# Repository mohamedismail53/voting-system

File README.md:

# About
Wireless Voting machine using Atmega32 and RF modules on PCB It consists of 4 separated PCB units: 3 transmitters and 1 receiver (every PCB unit has ATmega32 controller). Every transmitter block has 3 options to choose from (yes, no, abs) and the receiver has LCD that displays the result of every choice.

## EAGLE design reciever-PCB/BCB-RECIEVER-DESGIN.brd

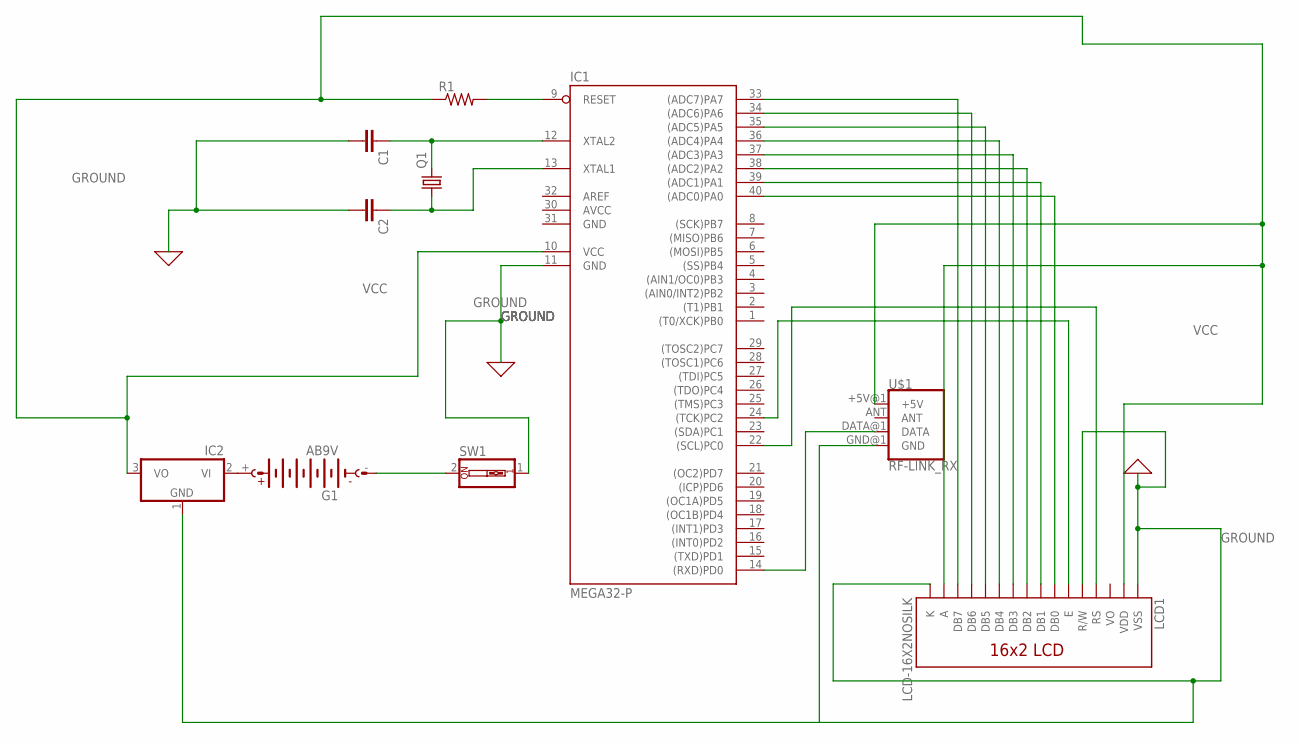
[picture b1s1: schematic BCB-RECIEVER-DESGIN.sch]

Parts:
C1, C2: C5/2.5; C5B2.5
G1: AB9V
IC1: MEGA32-P; DIL40
IC2: 7905T; TO220H
LCD1: LCD-16X2NOSILK; LCD-16X2_NOSILK
Q1: CRYSTALHC49S; HC49/S
R1: R-US_0207/10; 0207/10
SW1: SW_DIP-1; EDG-01
U$1: RF-LINK_RX

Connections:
AVCC: IC1.30 (AVCC)
GND: IC1.31 (GND)
GROUND: C1.2, C2.2, IC1.11 (GND), IC2.1 (GND), LCD1.1 (VSS), LCD1.5 (R/W), LCD1.16 (K), SW1.1, U$1.GND@1 (GND)
unnamed: IC1.9 (RESET), R1.2
unnamed: IC1.33 ((ADC7)PA7), LCD1.14 (DB7)
unnamed: IC1.34 ((ADC6)PA6), LCD1.13 (DB6)
unnamed: IC1.35 ((ADC5)PA5), LCD1.12 (DB5)
unnamed: IC1.36 ((ADC4)PA4), LCD1.11 (DB4)
unnamed: IC1.37 ((ADC3)PA3), LCD1.10 (DB3)
unnamed: IC1.38 ((ADC2)PA2), LCD1.9 (DB2)
unnamed: IC1.39 ((ADC1)PA1), LCD1.8 (DB1)
unnamed: IC1.40 ((ADC0)PA0), LCD1.7 (DB0)
unnamed: IC1.22 ((SCL)PC0), LCD1.4 (RS)
unnamed: IC1.24 ((TCK)PC2), LCD1.6 (E)
unnamed: IC1.14 ((RXD)PD0), U$1.DATA@1 (DATA)
unnamed: C2.1, IC1.13 (XTAL1), Q1.1
unnamed: C1.1, IC1.12 (XTAL2), Q1.2
unnamed: G1.+, IC2.2 (VI)
unnamed: G1.-, SW1.2
VCC: IC1.10 (VCC), IC2.3 (VO), LCD1.2 (VDD), LCD1.15 (A), R1.1, U$1.+5V@1 (+5V)

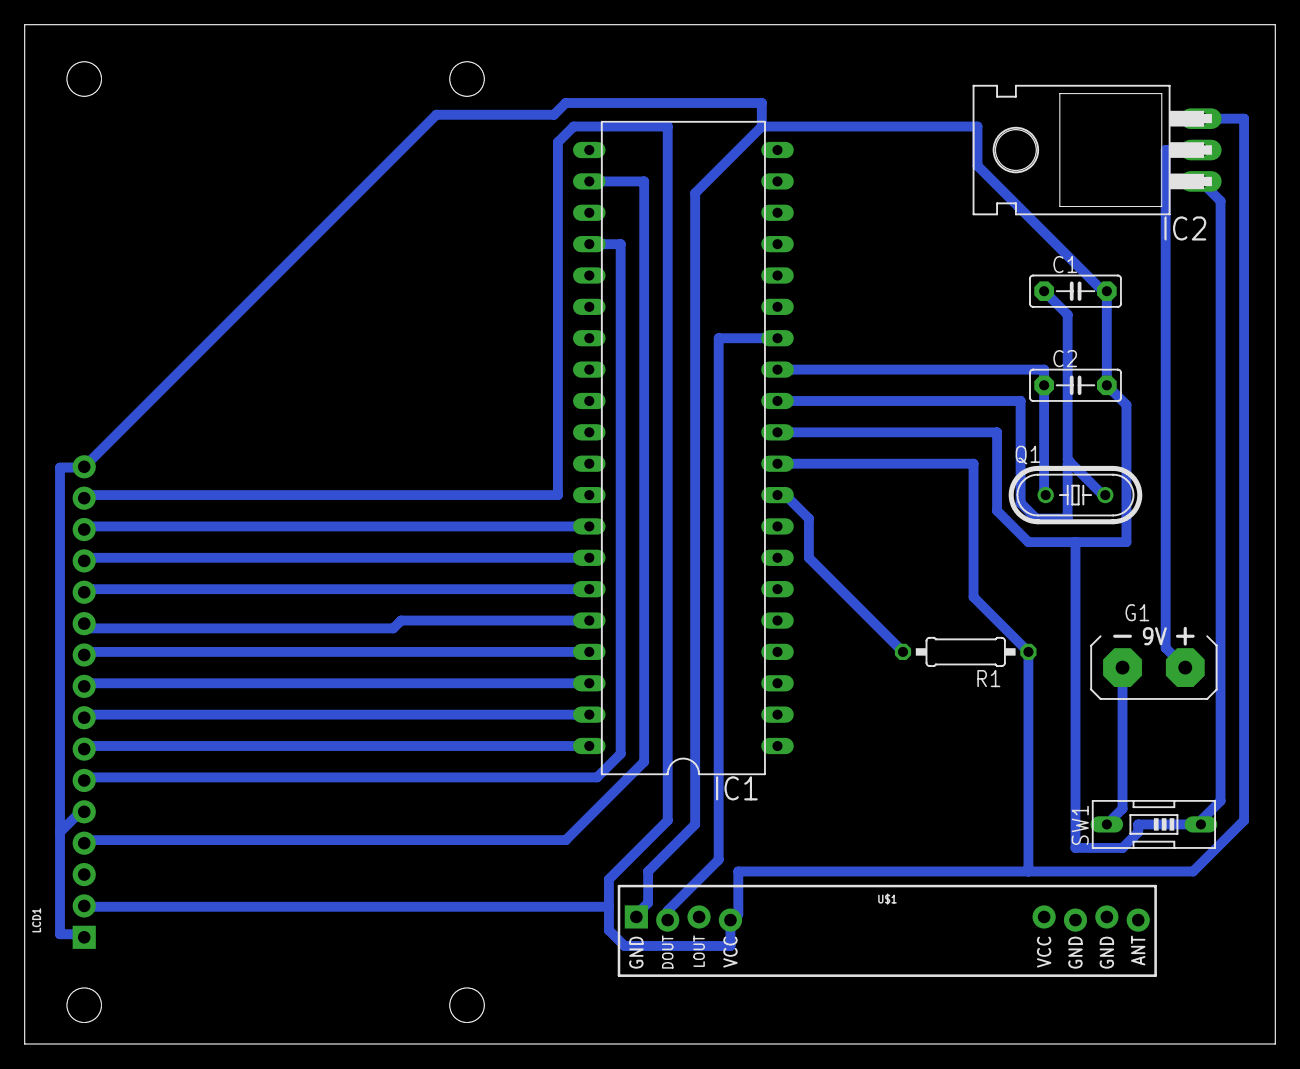
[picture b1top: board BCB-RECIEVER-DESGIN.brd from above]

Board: 2 copper layers, 101.3 x 82.5 mm, 10 parts (0 on the bottom side), 18 nets.

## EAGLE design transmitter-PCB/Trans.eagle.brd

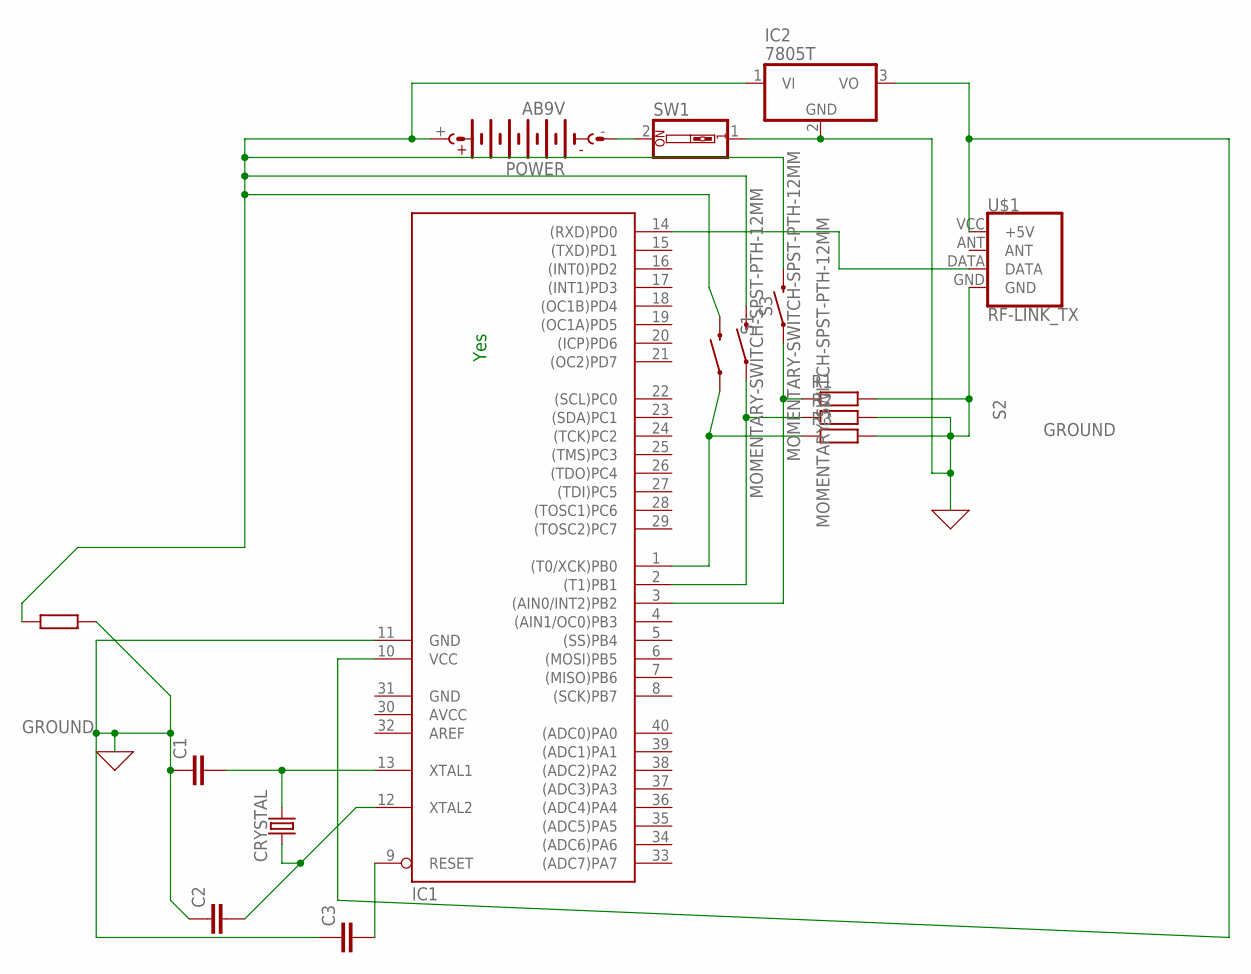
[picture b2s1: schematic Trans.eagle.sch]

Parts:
C1, C2, C3: 10nF; CAP-PTH-10MM
CRYSTAL: CRYSTALPTH-HC49UV; HC49U
IC1: MEGA32-P; DIL40
IC2: 7805T; TO220H
POWER: AB9V
R1, R2, R3, R4: R-EU_0309/12; 0309/12
S1, S2, S3: MOMENTARY-SWITCH-SPST-PTH-12MM; TACTILE_SWITCH_PTH_12MM
SW1: SW_DIP-1; EDG-01
U$1: RF-LINK_TX

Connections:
AVCC: IC1.30 (AVCC)
GND: IC1.31 (GND)
GROUND: C1.1, C2.1, C3.1, IC1.11 (GND), IC2.2 (GND), R1.2, R2.2, R3.2, R4.1, SW1.1, U$1.GND
unnamed: IC1.1 ((T0/XCK)PB0), R3.1, S2.1
unnamed: IC1.2 ((T1)PB1), R2.1, S1.1
unnamed: IC1.10 (VCC), IC2.3 (VO), U$1.VCC (+5V)
unnamed: IC1.3 ((AIN0/INT2)PB2), R1.1, S3.1
unnamed: C2.2, CRYSTAL.1, IC1.12 (XTAL2)
unnamed: POWER.-, SW1.2
unnamed: IC1.14 ((RXD)PD0), U$1.DATA
unnamed: C1.2, CRYSTAL.2, IC1.13 (XTAL1)
unnamed: C3.2, IC1.9 (RESET)
POWER: IC2.1 (VI), POWER.+, R4.2, S1.3 (2), S2.3 (2), S3.3 (2)

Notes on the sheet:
Yes

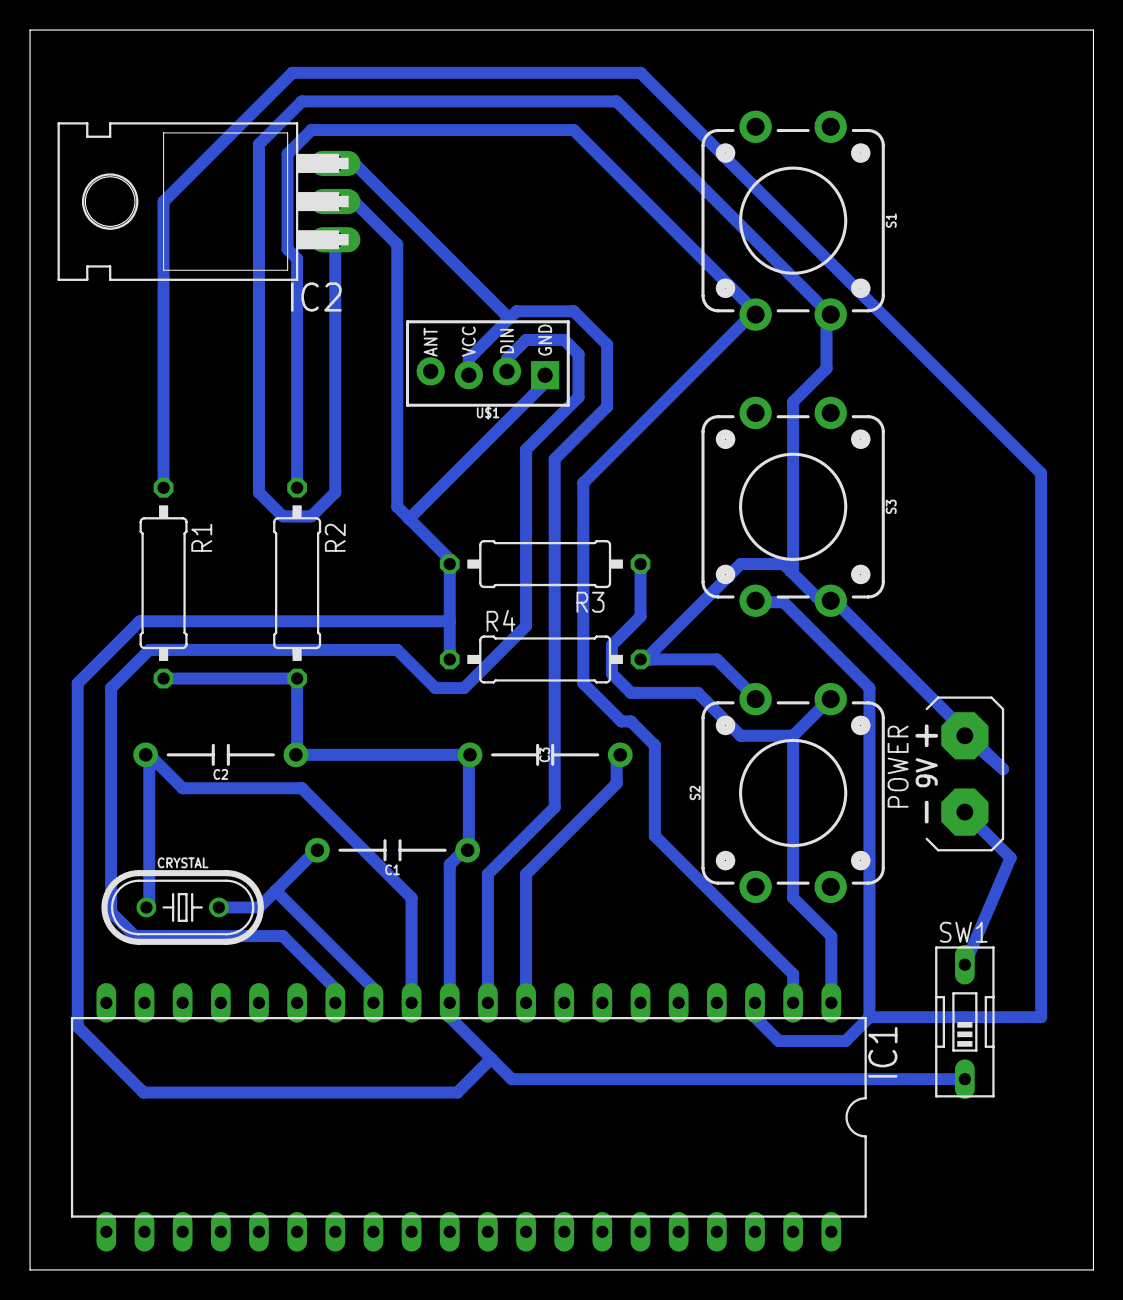
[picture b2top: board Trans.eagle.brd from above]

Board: 2 copper layers, 70.8 x 82.5 mm, 16 parts (0 on the bottom side), 11 nets.

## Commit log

2022-08-20 added-code-and-pcb-design
2022-08-20 added-README.md

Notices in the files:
parts and their libraries:
SparkFun-Displays: Licensing: Creative Commons ShareAlike 4.0 International - https://creativecommons.org/licenses/by-sa/4.0
